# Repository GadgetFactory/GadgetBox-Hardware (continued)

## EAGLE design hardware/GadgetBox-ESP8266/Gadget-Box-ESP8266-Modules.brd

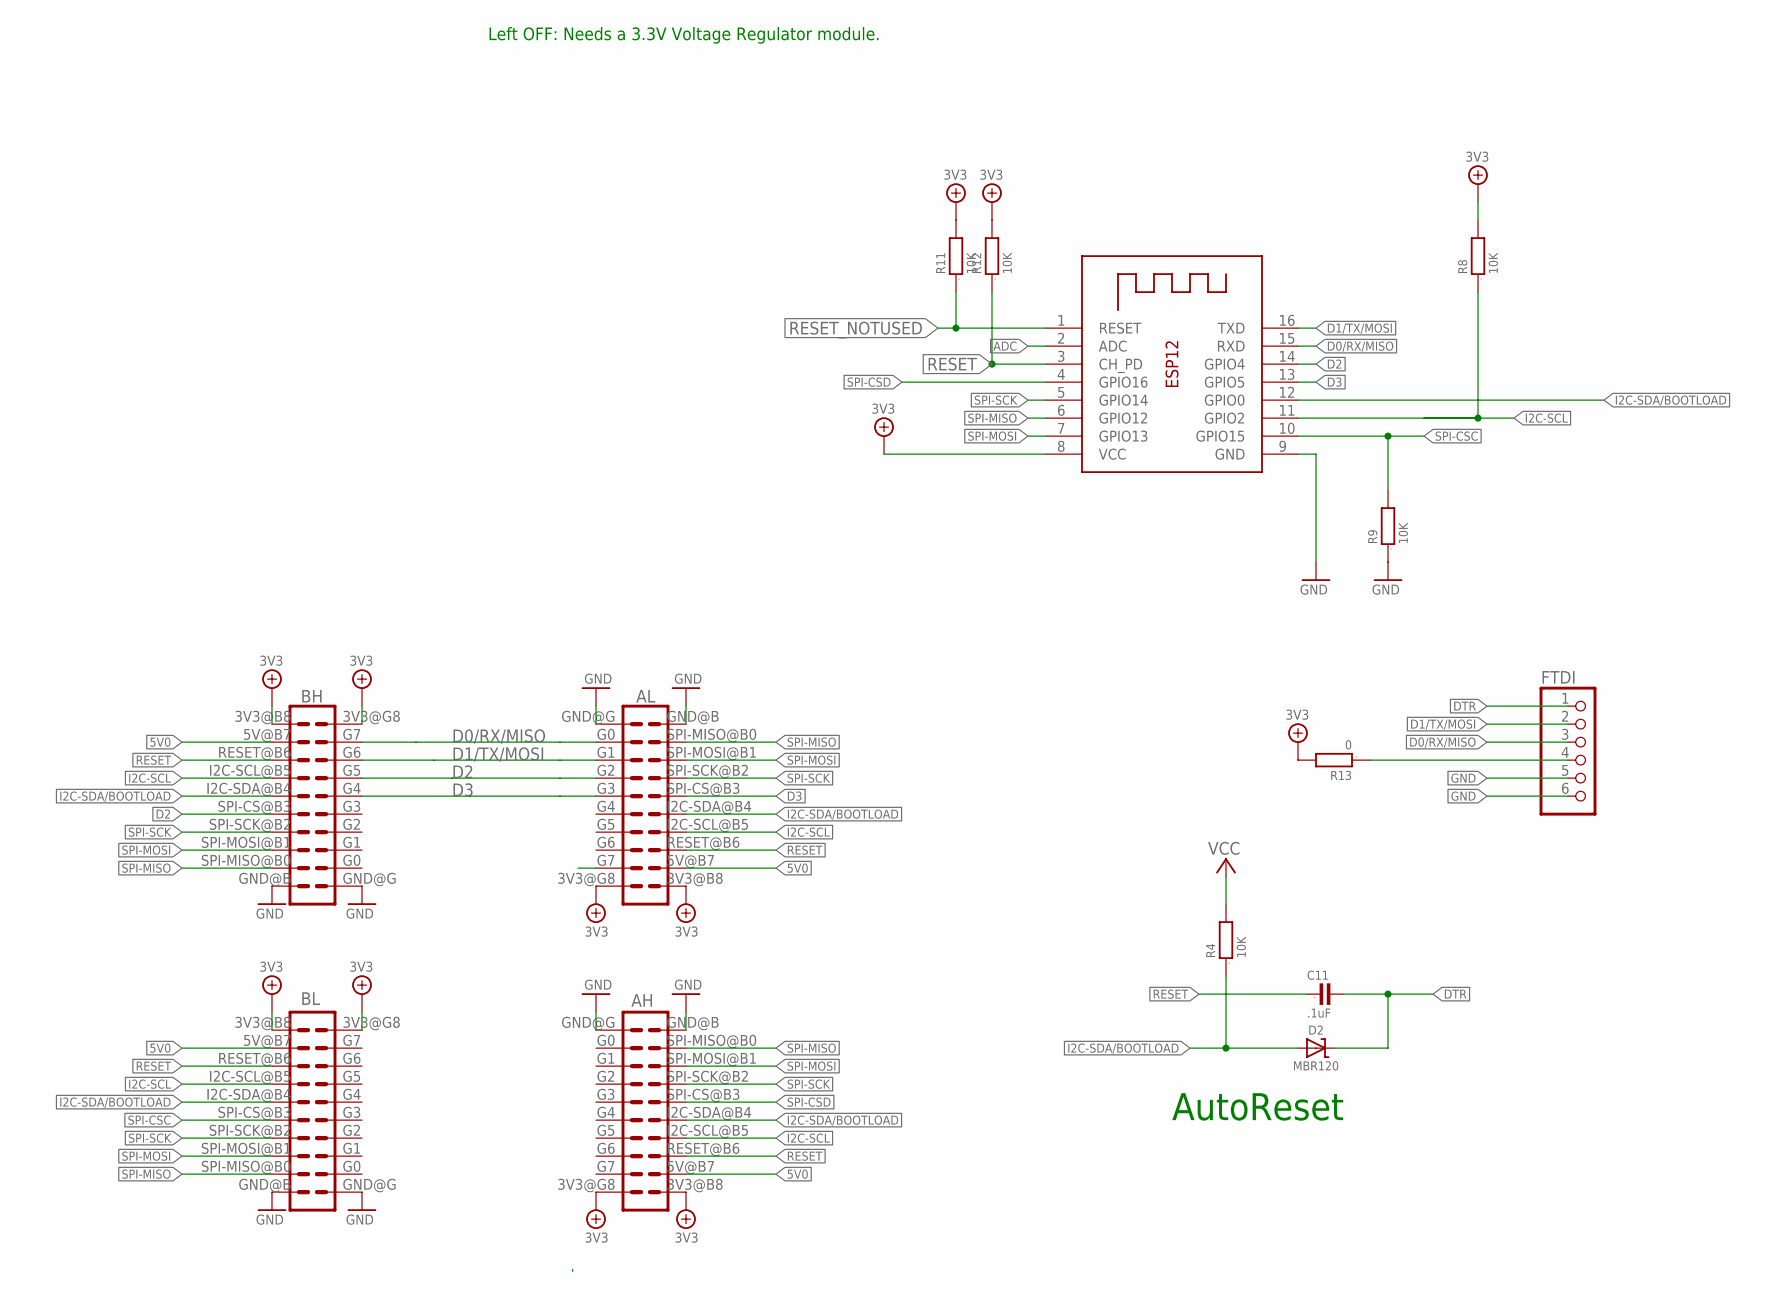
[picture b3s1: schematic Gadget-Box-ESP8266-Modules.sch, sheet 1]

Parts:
AH: ECOGECOG_SLOT; ECOG; PARTNO PPPC102LFBN-RC,SULLINS CONNECTOR SOLUTI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
AL: ECOGECOG_SLOT; ECOG; PARTNO PPPC102LFBN-RC,SULLINS CONNECTOR SOLUTI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
BH: ECOGECOG_SLOT; ECOG; PARTNO PPPC102LFBN-RC,SULLINS CONNECTOR SOLUTI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
BL: ECOGECOG_SLOT; ECOG; PARTNO PPPC102LFBN-RC,SULLINS CONNECTOR SOLUTI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
C11: .1uF; 0805; PARTNO GRM21BR71E104KA01L,MURATA ELECTRONICS (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
D2: MBR120; SOD-123; PARTNO MBR120VLSFT3G,on semiconductor,dk,MBR12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
FTDI: PINHD-1X6; 1X06; PARTNO PPPC061LGBN-RC,SULLINS CONNECTOR SOLUTI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
R4: 10K; 0805; PARTNO RC0805JR-0710KL,YAGEO (VA),dk,311-10KAR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
R8, R9, R11, R12: 10K; 0805; PARTNO RC0805JR-0710KL,YAGEO (VA),dk,311-10KAR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; DIGIKEY RMCF0805JT10K0CT-ND
R13: 0; 0805
X2: ESP-12; PARTNO 385646,AI-Thinker,dx.com,385646,ESP8266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

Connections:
3V3: AH.3V3@B8 (3V3), AH.3V3@G8 (3V3), AL.3V3@B8 (3V3), AL.3V3@G8 (3V3), BH.3V3@B8 (3V3), BH.3V3@G8 (3V3), BL.3V3@B8 (3V3), BL.3V3@G8 (3V3), R8.2, R11.2, R12.2, R13.2, X2.8 (VCC); also elsewhere on the board
5V0: AH.5V@B7 (5V), AL.5V@B7 (5V), BH.5V@B7 (5V), BL.5V@B7 (5V)
ADC: X2.2 (ADC); also elsewhere on the board
D0/RX/MISO: AL.G0, BH.G7, FTDI.3, X2.15 (RXD)
D1/TX/MOSI: AL.G1, BH.G6, FTDI.2, X2.16 (TXD)
D2: AL.G2, BH.G5, BH.SPI-CS@B3 (SPI-CS), X2.14 (GPIO4)
D3: AL.G3, AL.SPI-CS@B3 (SPI-CS), BH.G4, X2.13 (GPIO5)
DTR: C11.2, D2.C, FTDI.1
GND: AH.GND@B (GND), AH.GND@G (GND), AL.GND@B (GND), AL.GND@G (GND), BH.GND@B (GND), BH.GND@G (GND), BL.GND@B (GND), BL.GND@G (GND), FTDI.5, FTDI.6, R9.1, X2.9 (GND); also elsewhere on the board
I2C-SCL: AH.I2C-SCL@B5 (I2C-SCL), AL.I2C-SCL@B5 (I2C-SCL), BH.I2C-SCL@B5 (I2C-SCL), BL.I2C-SCL@B5 (I2C-SCL), R8.1, X2.11 (GPIO2)
I2C-SDA/BOOTLOAD: AH.I2C-SDA@B4 (I2C-SDA), AL.I2C-SDA@B4 (I2C-SDA), BH.I2C-SDA@B4 (I2C-SDA), BL.I2C-SDA@B4 (I2C-SDA), D2.A, R4.1, X2.12 (GPIO0)
unnamed: FTDI.4, R13.1
RESET: AH.RESET@B6 (RESET), AL.RESET@B6 (RESET), BH.RESET@B6 (RESET), BL.RESET@B6 (RESET), C11.1, R12.1, X2.3 (CH_PD)
RESET_NOTUSED: R11.1, X2.1 (RESET)
SPI-CSC: BL.SPI-CS@B3 (SPI-CS), R9.2, X2.10 (GPIO15)
SPI-CSD: AH.SPI-CS@B3 (SPI-CS), X2.4 (GPIO16)
SPI-MISO: AH.SPI-MISO@B0 (SPI-MISO), AL.SPI-MISO@B0 (SPI-MISO), BH.SPI-MISO@B0 (SPI-MISO), BL.SPI-MISO@B0 (SPI-MISO), X2.6 (GPIO12)
SPI-MOSI: AH.SPI-MOSI@B1 (SPI-MOSI), AL.SPI-MOSI@B1 (SPI-MOSI), BH.SPI-MOSI@B1 (SPI-MOSI), BL.SPI-MOSI@B1 (SPI-MOSI), X2.7 (GPIO13)
SPI-SCK: AH.SPI-SCK@B2 (SPI-SCK), AL.SPI-SCK@B2 (SPI-SCK), BH.SPI-SCK@B2 (SPI-SCK), BL.SPI-SCK@B2 (SPI-SCK), X2.5 (GPIO14)
VCC: R4.2

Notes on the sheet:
Left OFF: Needs a 3.3V Voltage Regulator module.
AutoReset

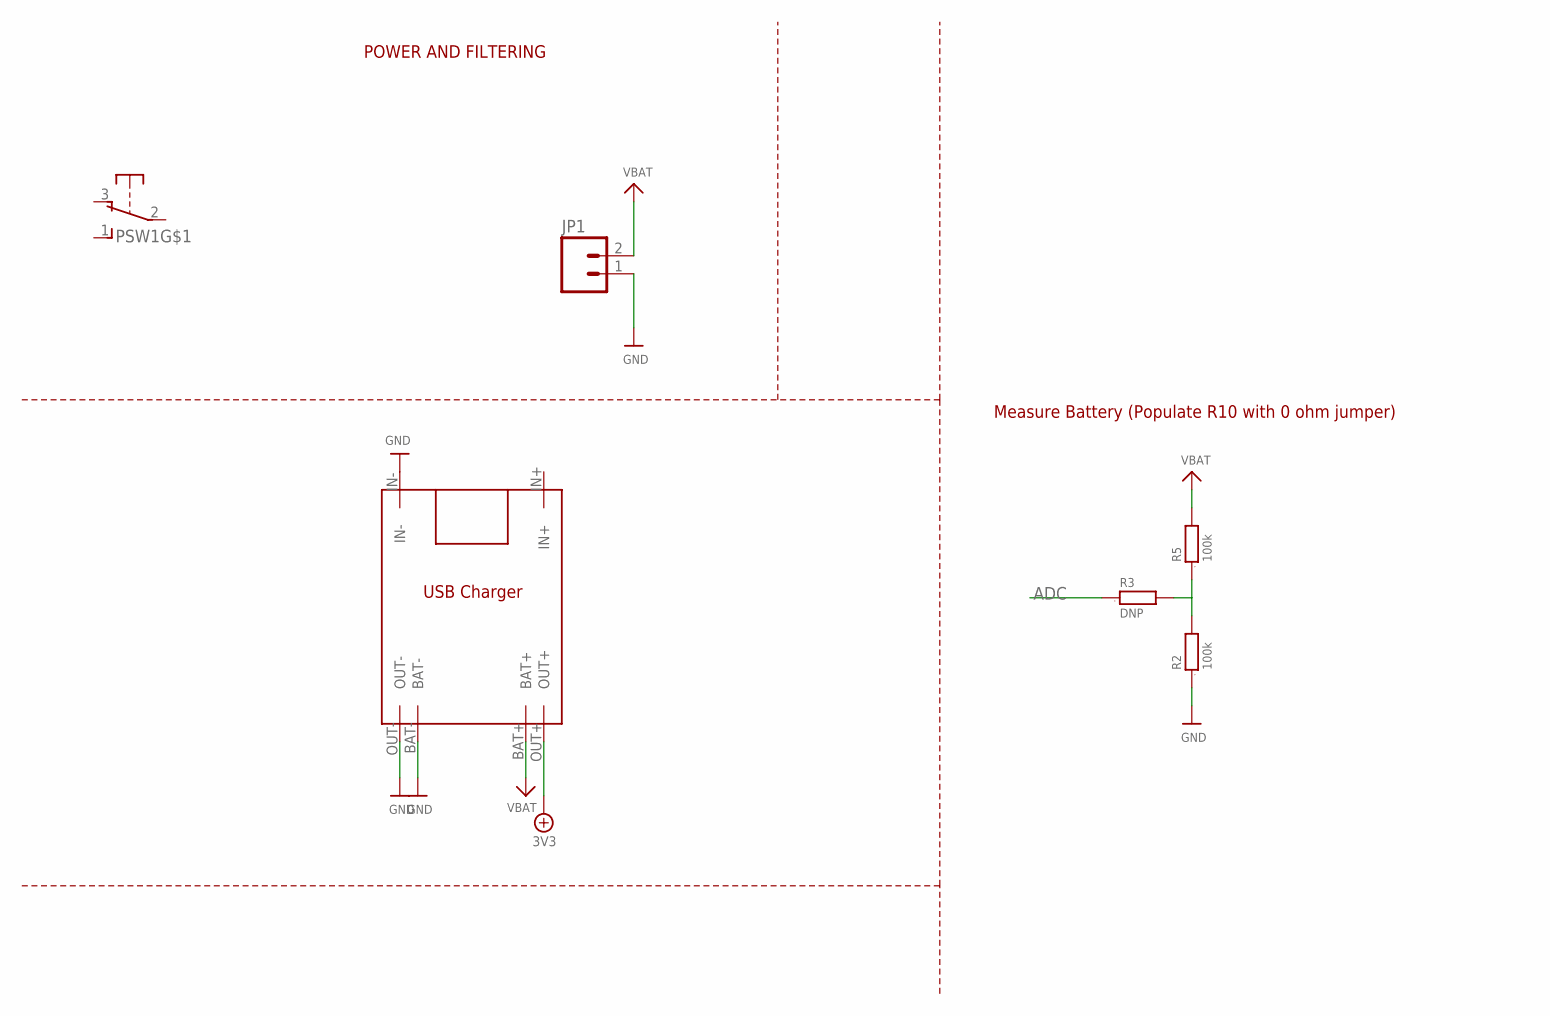
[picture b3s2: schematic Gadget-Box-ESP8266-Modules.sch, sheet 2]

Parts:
JP1: M02-JST-2-PTH-NO_SILK; JST-2-PTH-NS; PARTNO B2B-PH-SM4-TB(LF)(SN),JST SALES AMERICA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
PSW1: OS102011MA1Q; PARTNO OS102011MA1QN1,C&K Components,dk,CKN955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
R2, R5: 100k; 0603; PARTNO RC0603JR-07100KL,YAGEO (VA),dk,311-100K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
R3: DNP; 0603
U$1: TP4056

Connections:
3V3: U$1.OUT+; also elsewhere on the board
ADC: R3.1; also elsewhere on the board
GND: JP1.1, R2.1, U$1.BAT-, U$1.IN-, U$1.OUT-; also elsewhere on the board
unnamed: R2.2, R3.2, R5.1
VBAT: JP1.2, R5.2, U$1.BAT+

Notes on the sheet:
POWER AND FILTERING
Measure Battery (Populate R10 with 0 ohm jumper)

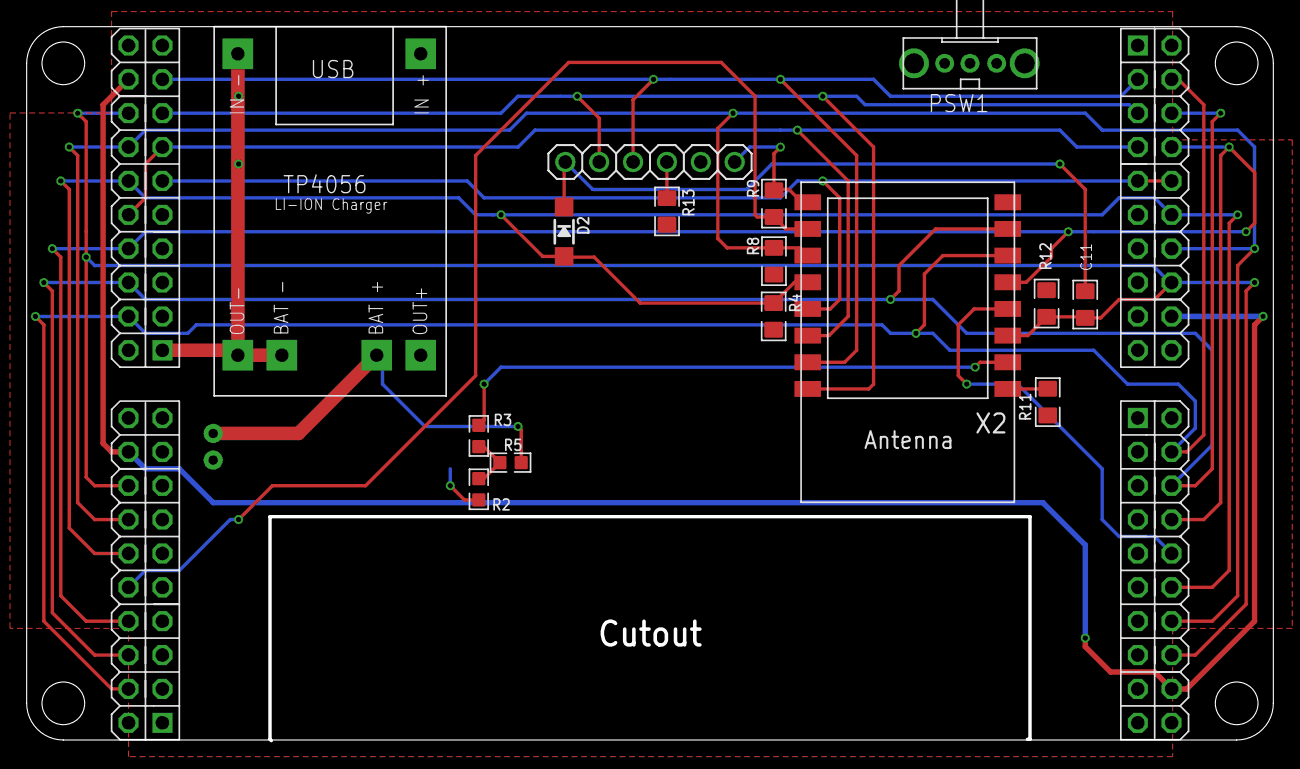
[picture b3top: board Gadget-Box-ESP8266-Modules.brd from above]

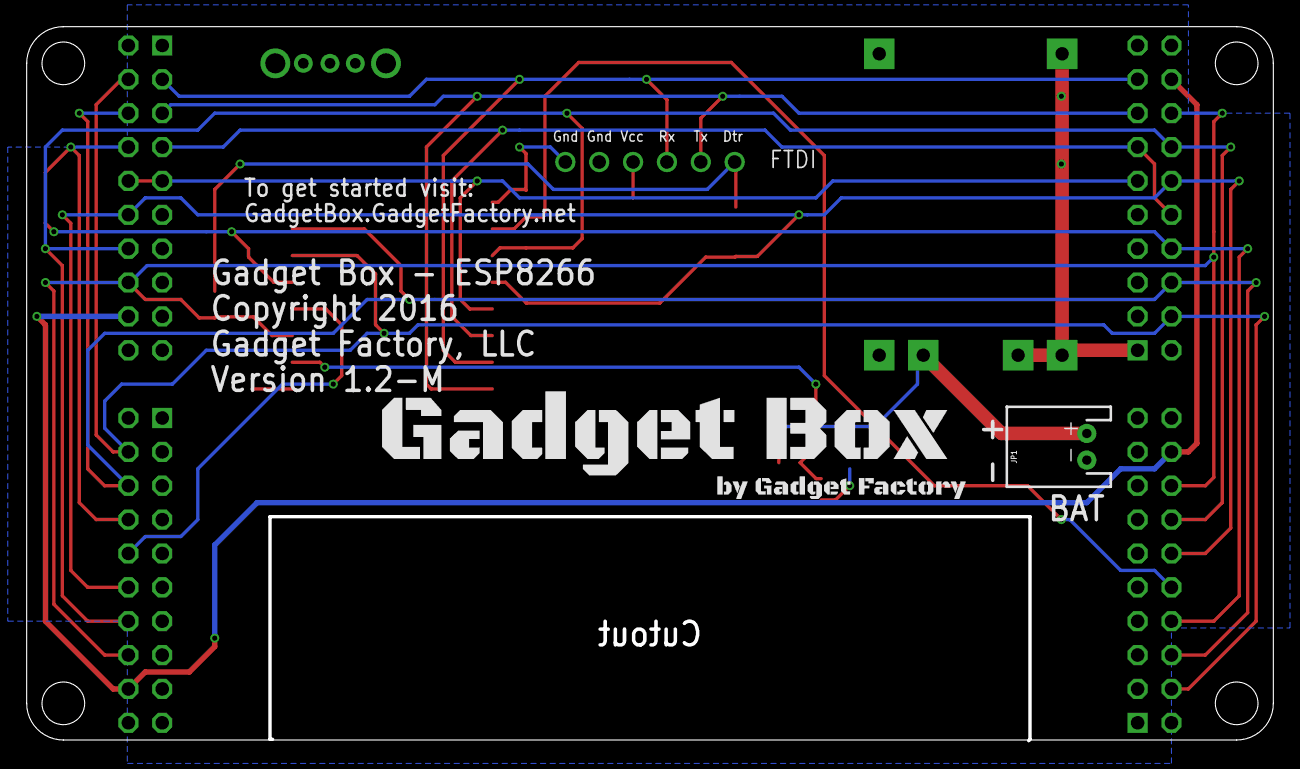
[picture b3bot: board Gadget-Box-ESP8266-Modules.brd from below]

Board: 2 copper layers, 93.2 x 53.4 mm, 22 parts (2 on the bottom side), 21 nets.

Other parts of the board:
$$U$1: ECOG93P53P5
U$100: GADGETBOX_TEXT

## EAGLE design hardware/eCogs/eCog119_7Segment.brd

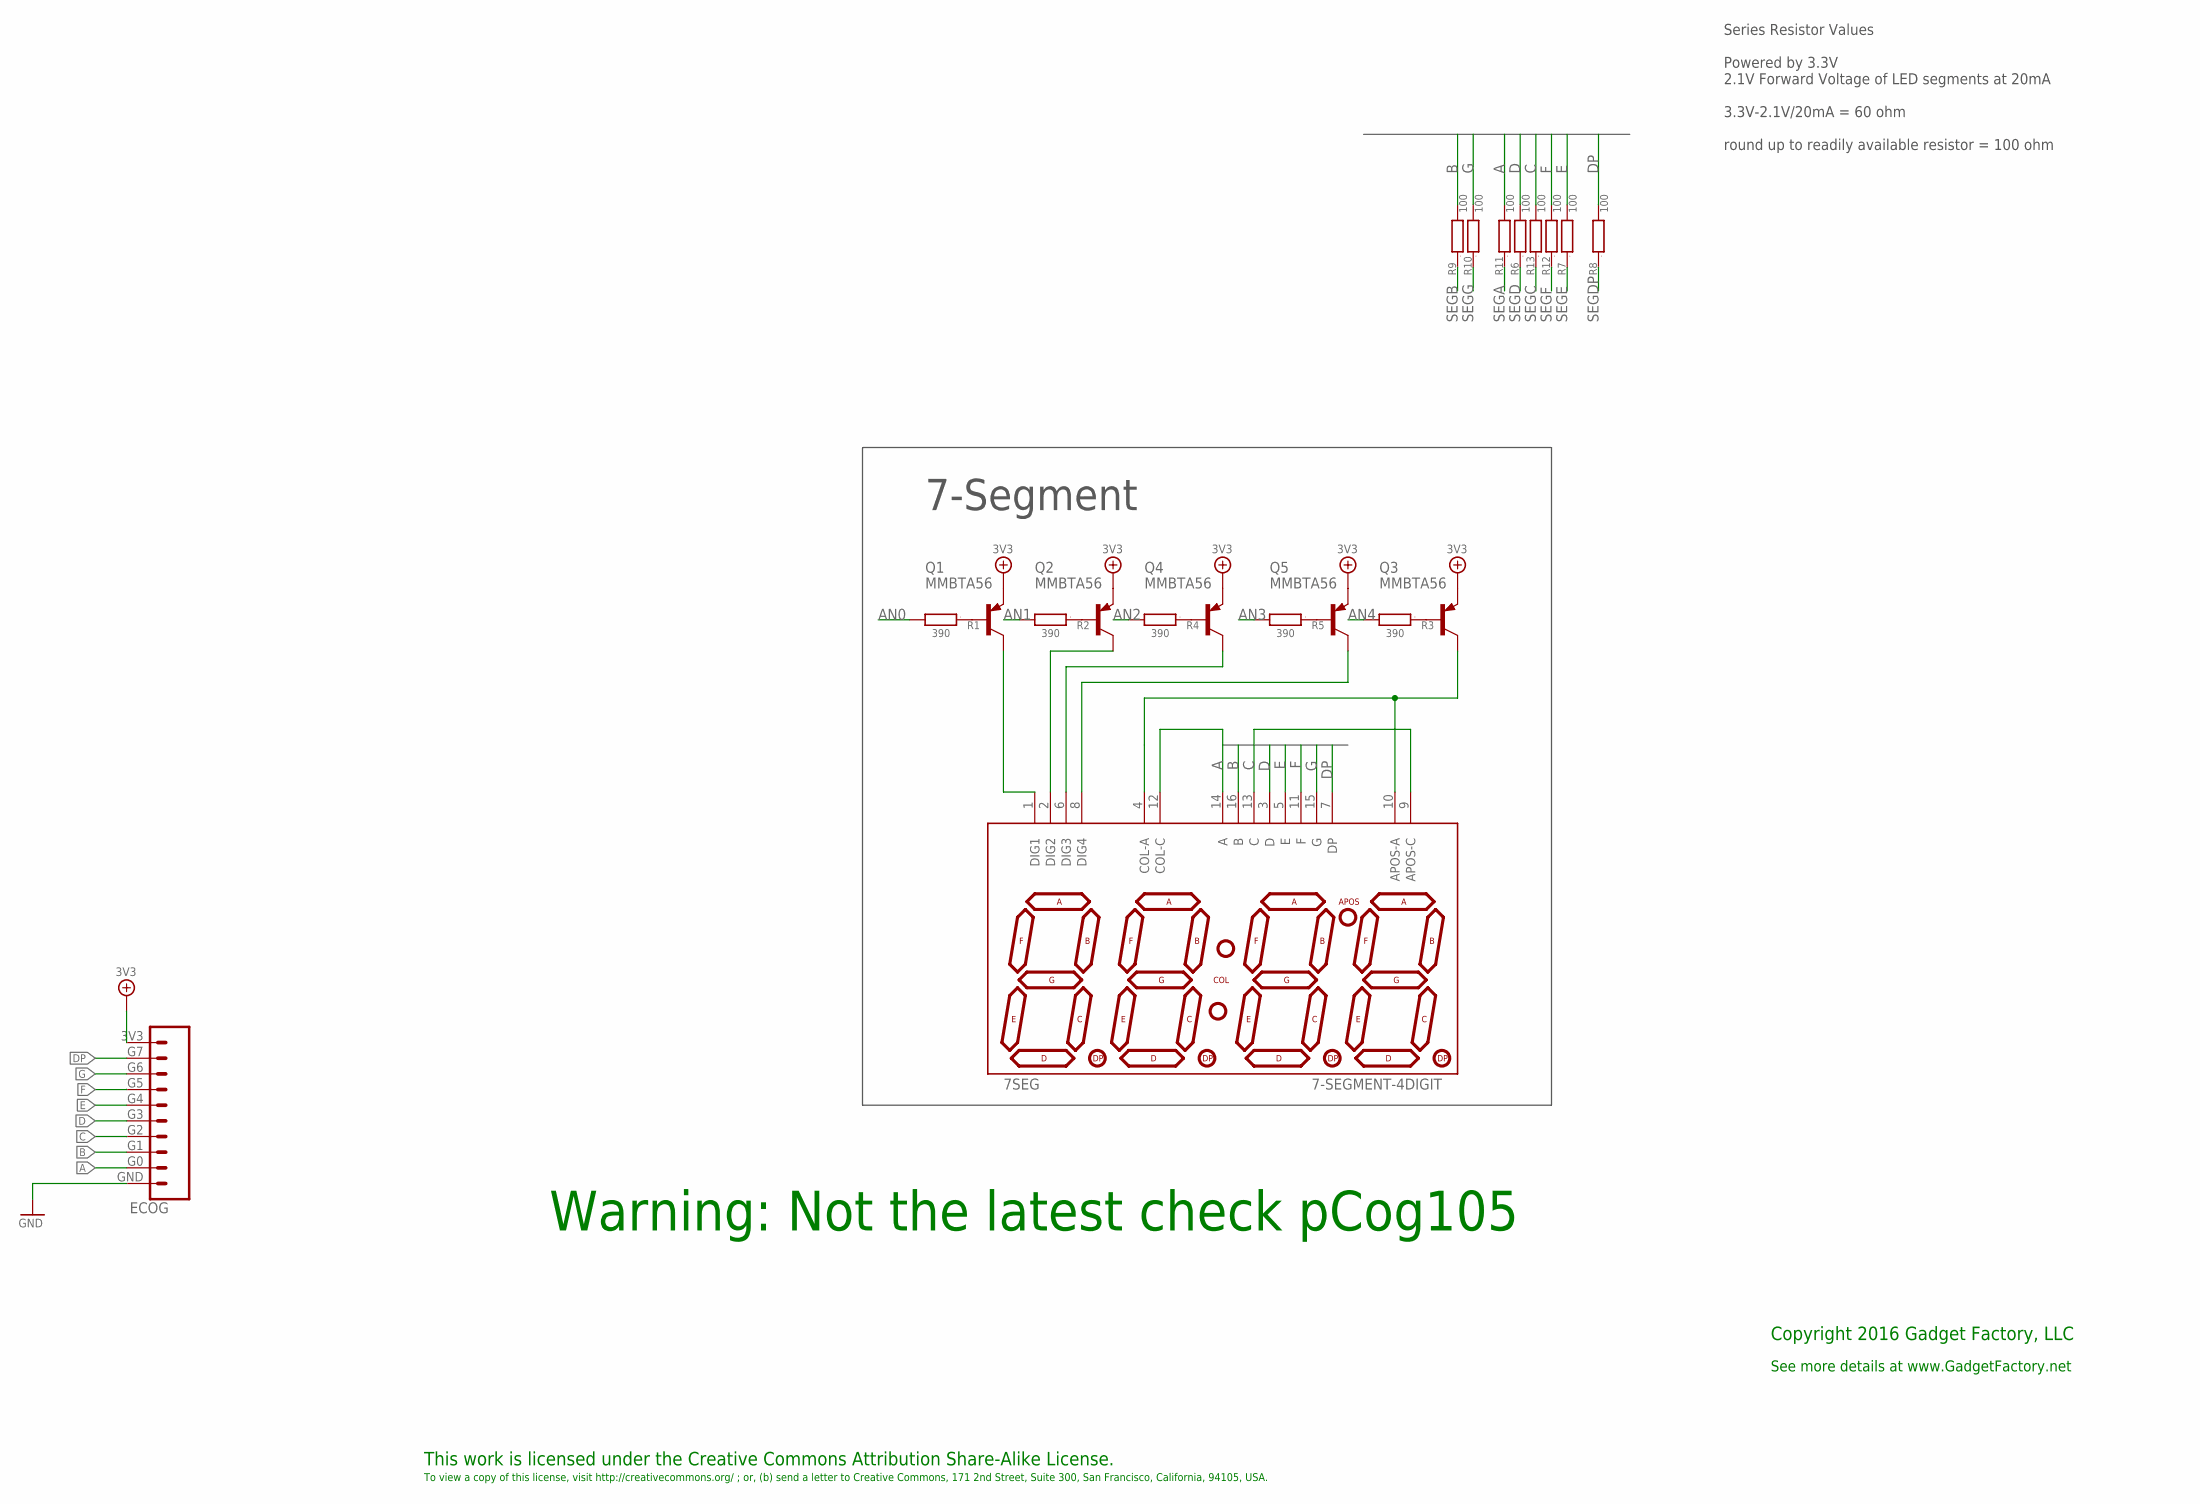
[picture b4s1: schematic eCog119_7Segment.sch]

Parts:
7SEG: 7-SEGMENT-4DIGIT; PARTNO AL-D4012BWSR/58-040C
ECOG: ECOG_GENERAL_ROWTHROUGHOLE; ECOG_GENERAL_TH
Q1, Q2, Q3, Q4, Q5: MMBTA56; SOT23; PARTNO MMBTA56
R1, R2, R3, R4, R5: 390; 0603; PARTNO CRCW0603100RJNEA
R6, R7, R8, R9, R10, R11, R12, R13: 100; 0603; PARTNO CRCW0603100RJNEA

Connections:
3V3: ECOG.3V3, Q1.2 (E), Q2.2 (E), Q3.2 (E), Q4.2 (E), Q5.2 (E)
A: 7SEG.12 (COL-C), 7SEG.14 (A), ECOG.G0, R11.2
AN0: R1.2
AN1: R2.2
AN2: R4.2
AN3: R5.2
AN4: R3.2
APOS_A: 7SEG.4 (COL-A), 7SEG.10 (APOS-A), Q3.3 (C)
B: 7SEG.16 (B), ECOG.G1, R9.2
C: 7SEG.9 (APOS-C), 7SEG.13 (C), ECOG.G2, R13.2
D: 7SEG.3 (D), ECOG.G3, R6.2
DP: 7SEG.7 (DP), ECOG.G7, R8.2
E: 7SEG.5 (E), ECOG.G4, R7.2
F: 7SEG.11 (F), ECOG.G5, R12.2
G: 7SEG.15 (G), ECOG.G6, R10.2
GND: ECOG.GND
unnamed: Q1.1 (B), R1.1
unnamed: Q2.1 (B), R2.1
unnamed: Q4.1 (B), R4.1
unnamed: Q5.1 (B), R5.1
unnamed: Q3.1 (B), R3.1
unnamed: 7SEG.1 (DIG1), Q1.3 (C)
unnamed: 7SEG.2 (DIG2), Q2.3 (C)
unnamed: 7SEG.6 (DIG3), Q4.3 (C)
unnamed: 7SEG.8 (DIG4), Q5.3 (C)
SEGA: R11.1
SEGB: R9.1
SEGC: R13.1
SEGD: R6.1
SEGDP: R8.1
SEGE: R7.1
SEGF: R12.1
SEGG: R10.1

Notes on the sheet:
This work is licensed under the Creative Commons Attribution Share-Alike License.
To view a copy of this license, visit http://creativecommons.org/ ; or, (b) send a letter to Creative Commons, 171 2nd Street, Suite 300, San Francisco, California, 94105, USA.
Copyright 2016 Gadget Factory, LLC
See more details at www.GadgetFactory.net
7-Segment
Series Resistor Values Powered by 3.3V 2.1V Forward Voltage of LED segments at 20mA 3.3V-2.1V/20mA = 60 ohm round up to readily available resistor = 100 ohm
Warning: Not the latest check pCog105

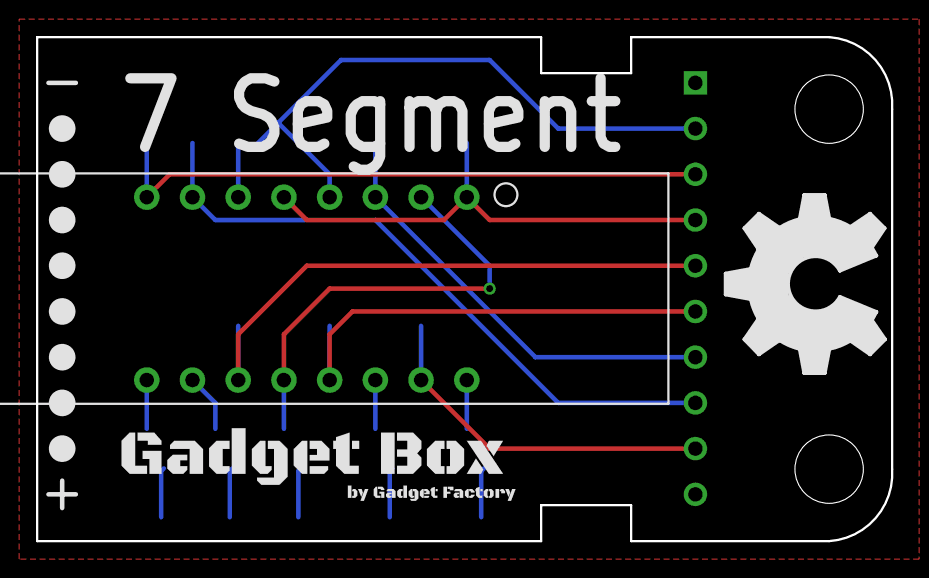
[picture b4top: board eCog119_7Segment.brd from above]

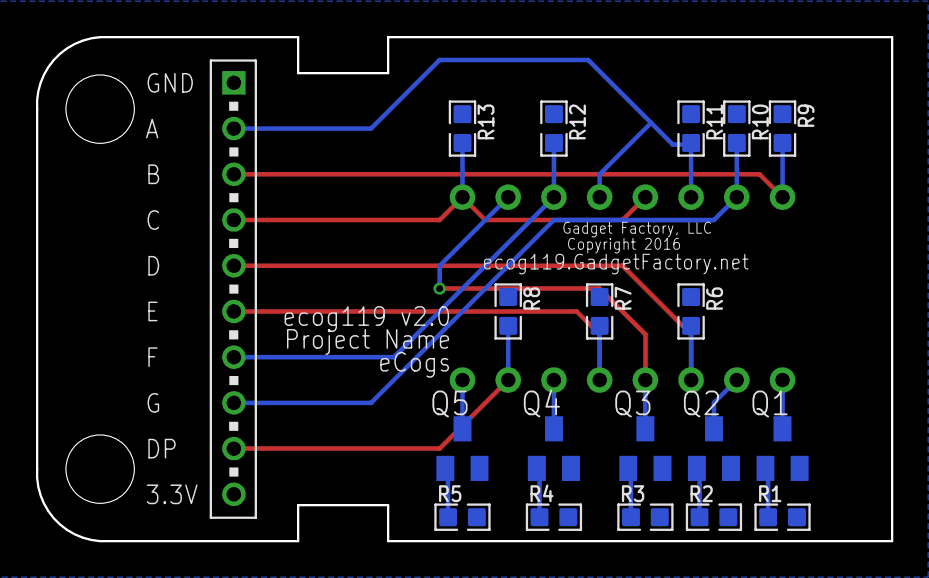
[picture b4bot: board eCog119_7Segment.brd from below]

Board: 2 copper layers, 47.5 x 28.0 mm, 30 parts (18 on the bottom side), 19 nets.

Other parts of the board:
U$1, U$2, U$4, U$5, U$6, U$7, U$8, U$9: LEGEND_DIO
U$3: OSHW_FILLX350_NOTEXT
U$10: GADGETBOX_SMALL

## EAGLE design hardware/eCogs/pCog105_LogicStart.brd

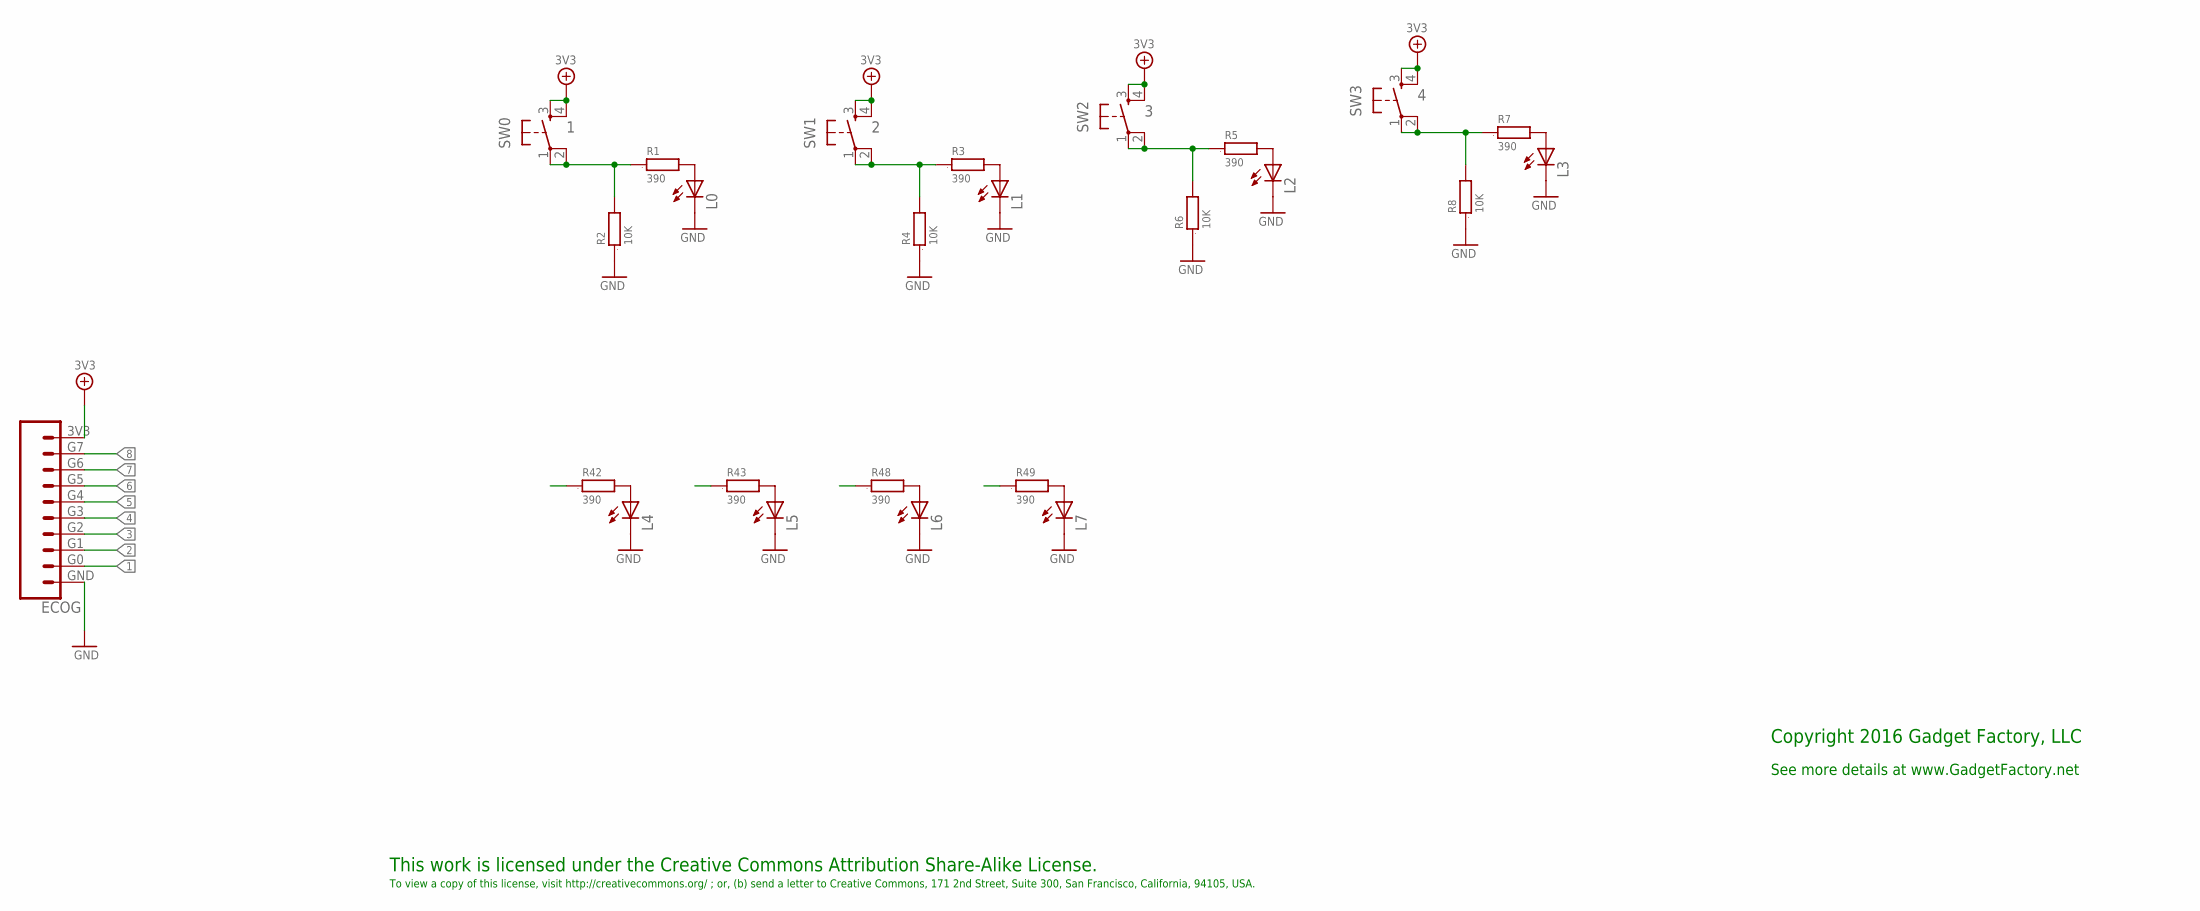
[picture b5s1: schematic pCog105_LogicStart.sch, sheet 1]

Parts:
ECOG: ECOG_GENERAL_ROWTHROUGHOLE; ECOG_GENERAL_TH
L0, L1, L2, L3, L4, L5, L6, L7: LEDCHIP-LED0805; CHIP-LED0805; DIGIKEY 475-1410-2-ND
R1, R3, R5, R7, R42, R43, R48, R49: 390; 0805; DIGIKEY RMCF0805JT390RCT-ND
R2, R4, R6, R8: 10K; 0805; DIGIKEY RMCF0805JT10K0CT-ND
SW0, SW1, SW2, SW3: TAC_SWITCHPTH; TACTILE-PTH; DIGIKEY 679-2428-ND

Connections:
1: ECOG.G0, R1.1, R2.2, SW0.1, SW0.2
2: ECOG.G1, R3.1, R4.2, SW1.1, SW1.2
3: ECOG.G2, R5.1, R6.2, SW2.1, SW2.2
3V3: ECOG.3V3, SW0.3, SW0.4, SW1.3, SW1.4, SW2.3, SW2.4, SW3.3, SW3.4; also elsewhere on the board
4: ECOG.G3, R7.1, R8.2, SW3.1, SW3.2
5: ECOG.G4, R42.1
6: ECOG.G5, R43.1
7: ECOG.G6, R48.1
8: ECOG.G7, R49.1
GND: ECOG.GND, L0.C, L1.C, L2.C, L3.C, L4.C, L5.C, L6.C, L7.C, R2.1, R4.1, R6.1, R8.1; also elsewhere on the board
unnamed: L0.A, R1.2
unnamed: L1.A, R3.2
unnamed: L2.A, R5.2
unnamed: L3.A, R7.2
unnamed: L4.A, R42.2
unnamed: L5.A, R43.2
unnamed: L6.A, R48.2
unnamed: L7.A, R49.2

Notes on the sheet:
This work is licensed under the Creative Commons Attribution Share-Alike License.
To view a copy of this license, visit http://creativecommons.org/ ; or, (b) send a letter to Creative Commons, 171 2nd Street, Suite 300, San Francisco, California, 94105, USA.
Copyright 2016 Gadget Factory, LLC
See more details at www.GadgetFactory.net

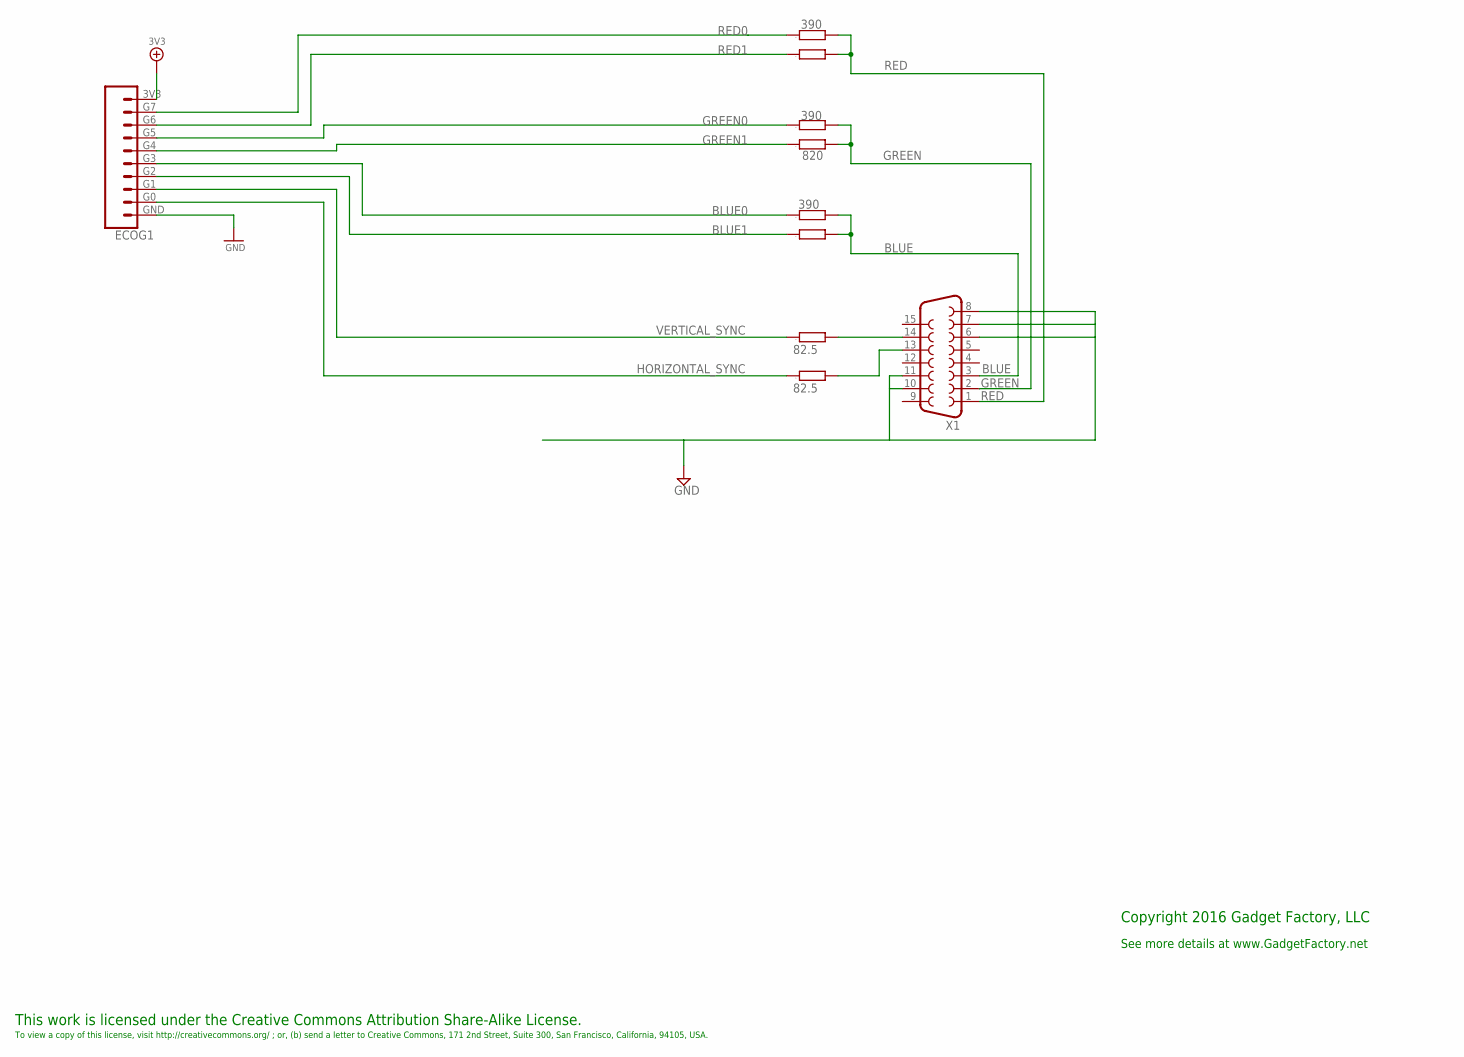
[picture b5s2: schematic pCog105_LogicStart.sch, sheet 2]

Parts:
ECOG1: ECOG_GENERAL_ROWTHROUGHOLE; ECOG_GENERAL_TH
R34, R41, R45: 390; 0603; PARTNO RMCF0603JT3K90
R35, R40, R44: 820; 0603; PARTNO RMCF0603JT2K00
R46, R47: 82.5; 0603; PARTNO RMCF0603FT82R5
X1: F15HDH; HDF15H; PARTNO 1-1734530-1

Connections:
3V3: ECOG1.3V3; also elsewhere on the board
BLUE: R44.2, R45.2, X1.3
BLUE0: ECOG1.G3, R45.1
BLUE1: ECOG1.G2, R44.1
GND: ECOG1.GND, X1.6, X1.7, X1.8, X1.10, X1.11; also elsewhere on the board
GREEN: R40.2, R41.2, X1.2
GREEN0: ECOG1.G5, R41.1
GREEN1: ECOG1.G4, R40.1
HORIZONTAL_SYNC: ECOG1.G0, R47.1
unnamed: R47.2, X1.13
unnamed: R46.2, X1.14
RED: R34.2, R35.2, X1.1
RED0: ECOG1.G7, R34.1
RED1: ECOG1.G6, R35.1
VERTICAL_SYNC: ECOG1.G1, R46.1

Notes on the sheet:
This work is licensed under the Creative Commons Attribution Share-Alike License.
To view a copy of this license, visit http://creativecommons.org/ ; or, (b) send a letter to Creative Commons, 171 2nd Street, Suite 300, San Francisco, California, 94105, USA.
Copyright 2016 Gadget Factory, LLC
See more details at www.GadgetFactory.net

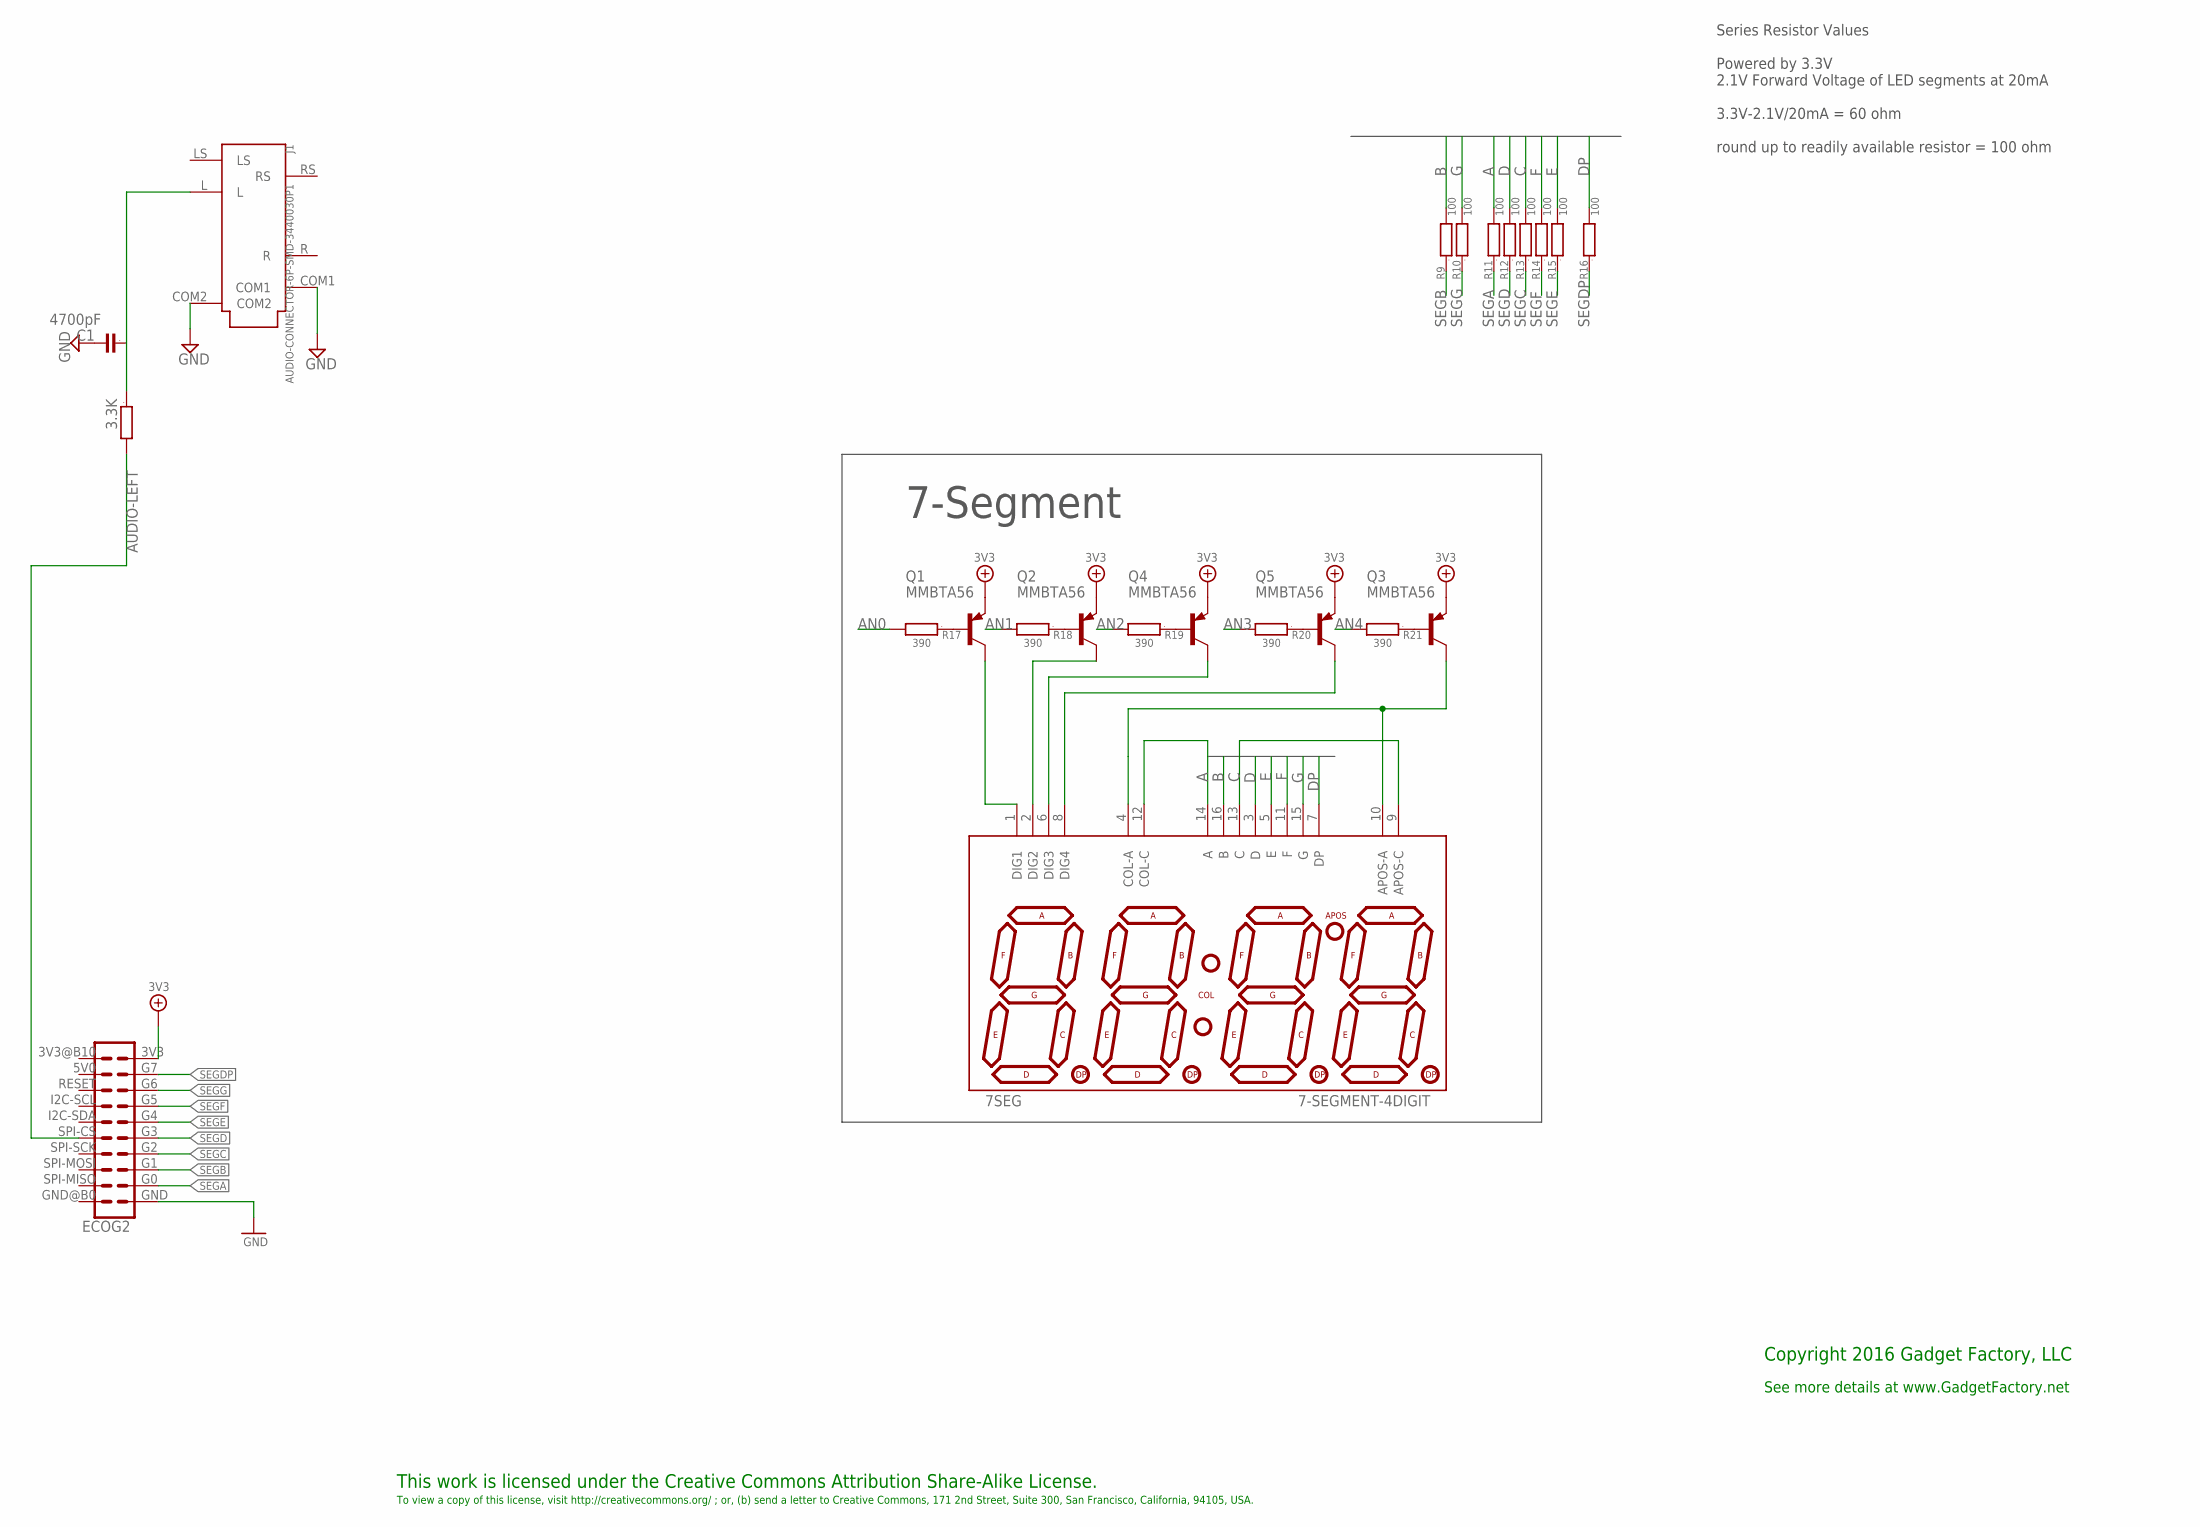
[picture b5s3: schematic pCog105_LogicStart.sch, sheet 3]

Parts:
7SEG: 7-SEGMENT-4DIGIT; PARTNO AL-D4012BWSR/58-040C
C1: 4700pF; 0603; PARTNO C0603C472J5RACTU
ECOG2: ECOG_DUALTHROUGHHOLE; ECOG_DUAL_TH
J1: AUDIO-CONNECTOR-6P-SMD-3440030P1; 6P-SMD-3.5; PARTNO 3440030P1
Q1, Q2, Q3, Q4, Q5: MMBTA56; SOT23; PARTNO MMBTA56
R9, R10, R11, R12, R13, R14, R15, R16: 100; 0603; PARTNO CRCW0603100RJNEA
R17, R18, R19, R20, R21: 390; 0603; PARTNO CRCW0603100RJNEA
R39: 3.3K; 0603; PARTNO RMCF0603JT3K30

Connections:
3V3: ECOG2.3V3, Q1.2 (E), Q2.2 (E), Q3.2 (E), Q4.2 (E), Q5.2 (E); also elsewhere on the board
A: 7SEG.12 (COL-C), 7SEG.14 (A), R11.2
AN0: R17.2
AN1: R18.2
AN2: R19.2
AN3: R20.2
AN4: R21.2
APOS_A: 7SEG.4 (COL-A), 7SEG.10 (APOS-A), Q3.3 (C)
AUDIO-LEFT: ECOG2.SPI-CS, R39.2
B: 7SEG.16 (B), R9.2
C: 7SEG.9 (APOS-C), 7SEG.13 (C), R13.2
D: 7SEG.3 (D), R12.2
DP: 7SEG.7 (DP), R16.2
E: 7SEG.5 (E), R15.2
F: 7SEG.11 (F), R14.2
G: 7SEG.15 (G), R10.2
GND: C1.2, ECOG2.GND, J1.COM1, J1.COM2; also elsewhere on the board
unnamed: Q1.1 (B), R17.1
unnamed: Q2.1 (B), R18.1
unnamed: Q4.1 (B), R19.1
unnamed: Q5.1 (B), R20.1
unnamed: Q3.1 (B), R21.1
unnamed: C1.1, J1.L, R39.1
unnamed: 7SEG.1 (DIG1), Q1.3 (C)
unnamed: 7SEG.2 (DIG2), Q2.3 (C)
unnamed: 7SEG.6 (DIG3), Q4.3 (C)
unnamed: 7SEG.8 (DIG4), Q5.3 (C)
SEGA: ECOG2.G0, R11.1
SEGB: ECOG2.G1, R9.1
SEGC: ECOG2.G2, R13.1
SEGD: ECOG2.G3, R12.1
SEGDP: ECOG2.G7, R16.1
SEGE: ECOG2.G4, R15.1
SEGF: ECOG2.G5, R14.1
SEGG: ECOG2.G6, R10.1

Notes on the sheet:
This work is licensed under the Creative Commons Attribution Share-Alike License.
To view a copy of this license, visit http://creativecommons.org/ ; or, (b) send a letter to Creative Commons, 171 2nd Street, Suite 300, San Francisco, California, 94105, USA.
Copyright 2016 Gadget Factory, LLC
See more details at www.GadgetFactory.net
7-Segment
Series Resistor Values Powered by 3.3V 2.1V Forward Voltage of LED segments at 20mA 3.3V-2.1V/20mA = 60 ohm round up to readily available resistor = 100 ohm
